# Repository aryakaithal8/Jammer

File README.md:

# Jammer

Jammer is my custom handheld electronics project, built around an **ESP32-S3-WROOM-1-N16** with a main board, a separate shield and a custom enclosure.

so basically i wanted to make a handheld device with its own screen, buttons, battery and a proper case, but i also wanted to go further than just connecting a bunch of ready-made modules together.. custom schematics, a stacked PCB design, touch display, storage, infrared, status feedback and the firmware side too. i designed the electronics in KiCad and worked on the enclosure in Fusion 360, which turned into a much bigger rabbit hole than expected lol

## why i made this

i wanted to build something where i could work on the whole thing from scratch instead of only doing one small part of it.. the circuit, board layout, case, controls and the parts list all had to fit together into one handheld project

main goals :

- make the schematic section by section in KiCad
- design a main board and a separate shield that fit together as a stack
- include a 2.8-inch SPI touch display and six front buttons
- include USB-C connections and a USB-to-UART interface for development
- add storage, infrared and visual feedback to the design
- plan the battery and power sections around a portable device
- work through PCB placement and routing instead of stopping at the schematic
- design a custom enclosure in Fusion 360
- keep the project files, production references, images and BOM together so the work is easier to understand and build on

the fun part is that everything affects everything else.. changing a connector position can affect the routing and the case opening, while changing the display arrangement can affect the buttons, internal space and cable clearance. thats the kind of detail that makes a handheld project way more involved than it looks from the outside

whats in this repo :

- `CAD/` — exported assembly models and printing files
- `BOM Images/` — supplier and component sourcing screenshots
- `Firmware/` — MicroPython application files and the bundled runtime image
- `FusionFiles/` — editable Fusion 360 design file
- `Images/` — PCB, schematic and enclosure screenshots
- `PCB/` — KiCad projects, libraries, audit material and the separate engineering revision
- `PDFs/` — exported schematic and layout PDFs
- `Production/` — Gerber archives, placement information, BOM and netlist exports
- `bom.csv` — sourcing list, supplier links and captured costs

## hardware summary

| | |
|---|---|
| Project | Jammer |
| Format | Custom handheld device with stacked main and shield boards |
| Controller listed in BOM | ESP32-S3-WROOM-1-N16 |
| Display | Robu 62026 2.8-inch SPI touch display |
| Front controls | Six buttons shown in the project design |
| USB | Two USB-C receptacles listed in the BOM |
| Development interface | CP2102N USB-to-UART section |
| Button interface in earlier design | PCF8574 I/O expander |
| Storage | SD card socket included in the design |
| Infrared | IR emitter and receiver parts included in the project |
| Feedback | Status LEDs, addressable RGB and a buzzer section |
| Radio parts in the supplied design material | nRF24L01-family and CC1101 parts with external connector provisions |
| Power | Battery, charging and supply sections with revision-specific parts |
| PCB | Main board and shield, with four-layer fabrication files in the revised engineering package |
| CAD | Fusion 360 and exported 3D files |
| Firmware | MicroPython source with hardware limitations documented in the files |

some of the interesting work is hidden inside the enclosure.. the boards need to fit together, the display needs its own space and support, and the controls and connectors need to line up with the outside of the case. the CAD and PCB images below show the project from a few different angles

## images

### main PCB

### PCB routing and board layers

### shield PCB

### schematic

i worked on the schematic in smaller sections first, then brought those sections together before moving into the PCB layout. the screenshots include the controller, power, connectors, display, controls and supporting circuits from the supplied design material

### CAD and case

these are design screenshots and renders, so they show the intended arrangement rather than a finished physical assembly. some schematic images also show earlier revisions and should be read alongside the current files

## repo file checklist

the main project folder names are:

- `PCB/` — KiCad design files and engineering references
- `CAD/` — assembly exports and printing files
- `FusionFiles/` — editable Fusion design
- `Firmware/` — MicroPython source and runtime files
- `Production/` — manufacturing outputs
- `PDFs/` — schematic and layout exports
- `Images/` — project screenshots used in this README
- `BOM Images/` — sourcing screenshots
- `bom.csv` — captured sourcing list

the exact filenames inside each folder may change as the project gets updated, so open the folders to find the relevant versions. check the revision before combining a schematic, board, firmware file or parts list from different places

## cad

the case was designed in Fusion 360. [`FusionFiles/Jammer V1.f3d`](FusionFiles/Jammer%20V1.f3d) is the editable design, while `CAD/` contains the exported assembly and printing material. check the available files and formats before preparing a print or manufacturing order

the case and PCB need to be checked together before fabrication: board mounting, screen support, connector access, button alignment and space for the battery and cables all matter. something looking clear in the outside render doesnt automatically mean the internal assembly fits properly

the internal CAD view is useful for seeing how the parts are intended to sit together, but the actual display module, connector tolerances and battery clearance still need a physical fit check

## firmware note

the project includes a `Firmware/` folder with MicroPython files for the application, hardware interfaces, display, storage, infrared and radio-related code. it also includes an ESP32-S3 MicroPython runtime image and its provenance information

the application source includes menu and device-status handling, touch calibration, storage/logging support and interface-related functions. these are source-level features and still need to be checked on the actual hardware

the top-level `hardware.py` explicitly sets `RADIOS_AVAILABLE = False`. it also holds some conflicting functions inactive instead of pretending they are usable, so the presence of a menu item or driver file isnt proof that the matching hardware feature is ready

firmware configuration and flashing details should be confirmed against the actual files and the matching schematic revision before building. i dont want to claim a particular image, pin assignment or feature is ready until it has been checked against the board it is meant to run on

## bom

the sourcing bill of materials is in [`bom.csv`](bom.csv). it includes the item name, quantity, supplier link, distributor and total line cost in US dollars.
**listed BOM total: $459.58 USD**

a few notable parts from the BOM:

| Part | Purpose |
|---|---|
| ESP32-S3-WROOM-1-N16 | Main controller |
| Robu 62026 touch display | Screen and touch interface |
| CP2102N-A02-GQFN28R | USB-to-UART interface |
| PCF8574T | I/O expansion in the earlier design |
| TE Connectivity 2041021-3 | SD card socket |
| GCT USB4105-GF-A | USB-C receptacles |
| WS2812B-2020-V6 | Addressable RGB indicators |
| CMT-7525-80-SMT-TR | Buzzer listed in the sourcing list |
| TSAL6200 and TSOP1738 | Infrared-related parts |
| nRF24L01 and CC1101 parts | Radio hardware represented in the supplied design material |
| Main and shield PCB fabrication | Separate board orders listed in the CSV |
| Printed enclosure and mounting hardware | Case and assembly parts |

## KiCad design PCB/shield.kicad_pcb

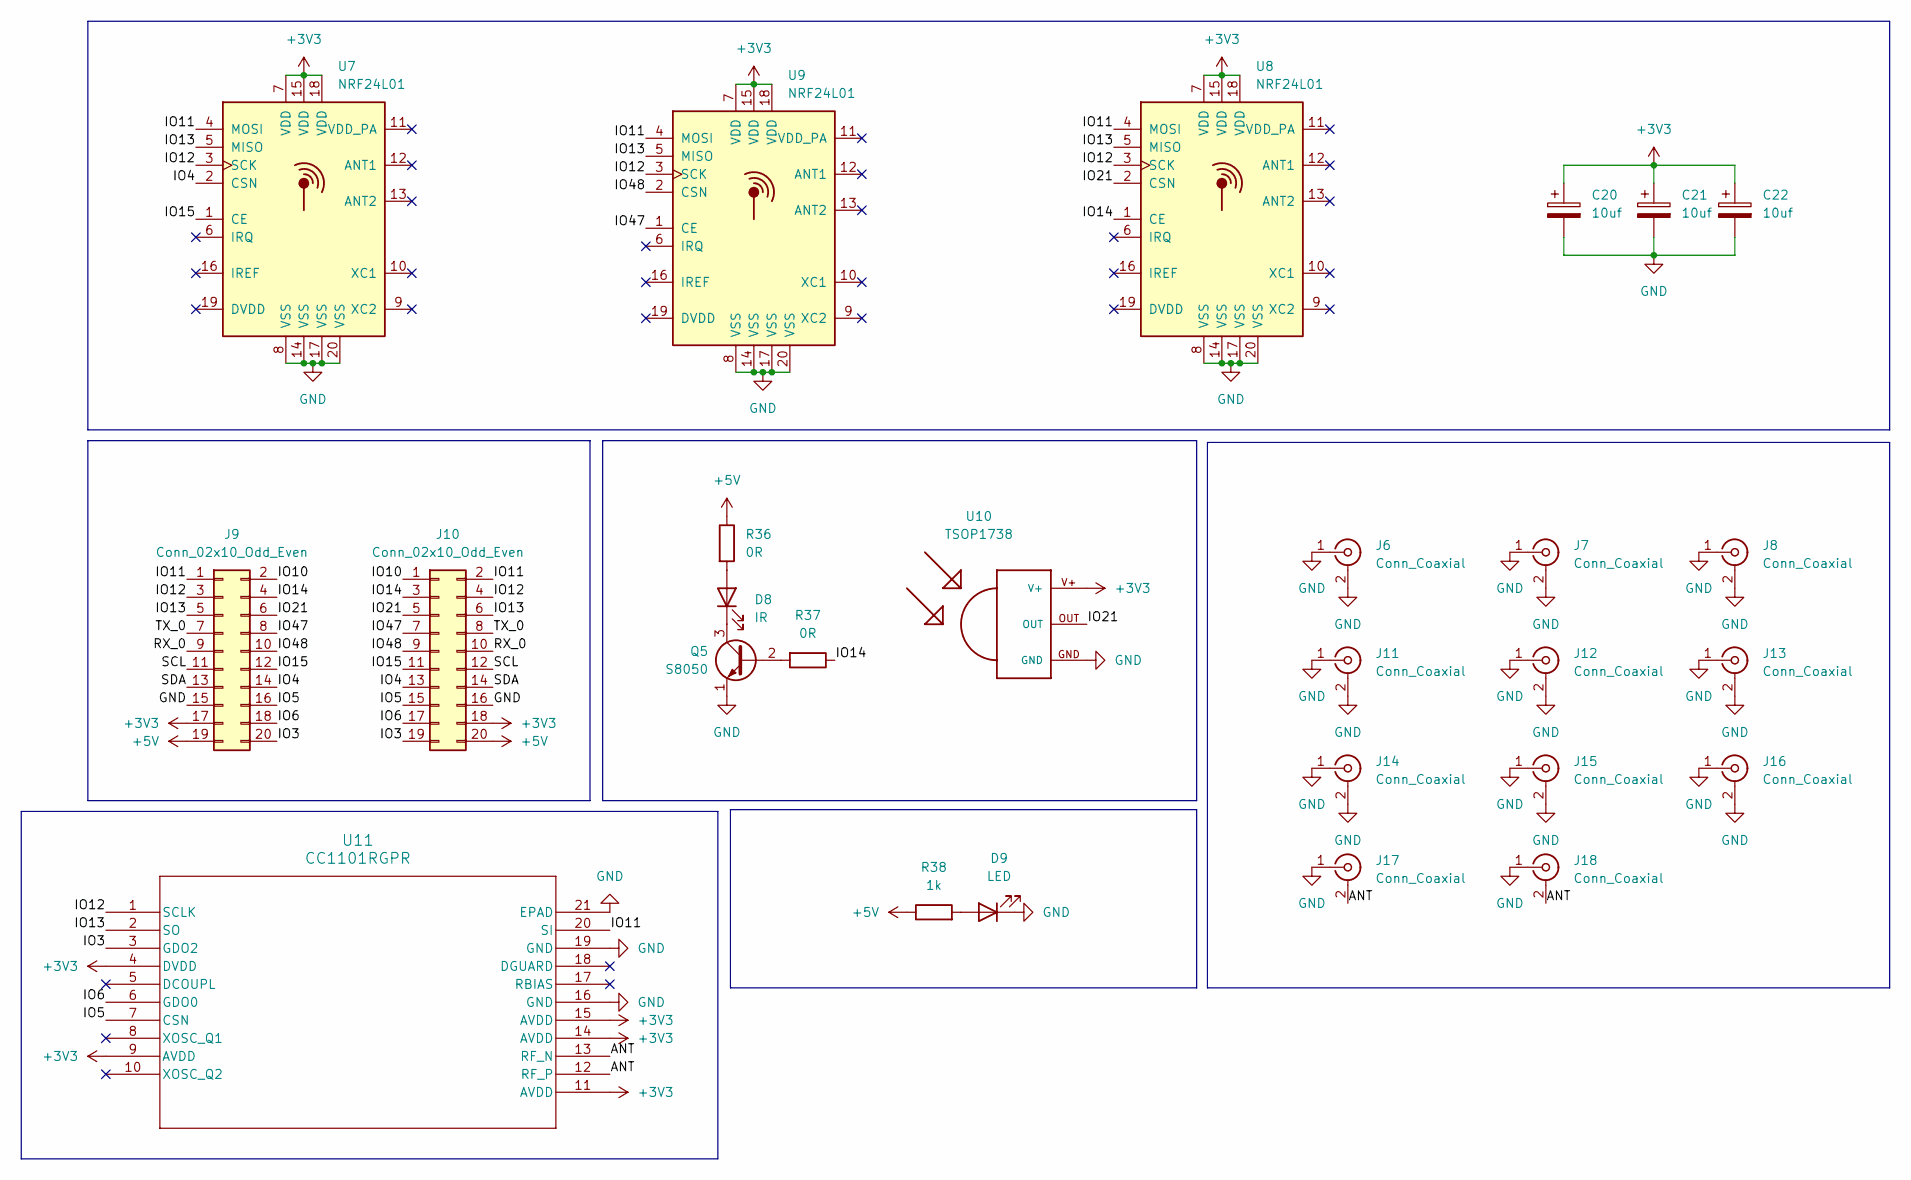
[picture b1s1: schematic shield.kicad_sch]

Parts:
C20, C21, C22: 10uf; C_0805_2012Metric
D8: IR; LED_D5.0mm
D9: LED; LED_0603_1608Metric
J6, J7, J8, J11, J12, J13, J14, J15, J16, J17, J18: Conn_Coaxial; SMA_Amphenol_132289_EdgeMount
J9, J10: Conn_02x10_Odd_Even; PinHeader_2x10_P2.54mm_Vertical
Q5: S8050; TO-92_Inline
R36, R37: 0R; R_0603_1608Metric
R38: 1k; R_0603_1608Metric
U7, U8, U9: NRF24L01; QFN-20-1EP_4x4mm_P0.5mm_EP2.5x2.5mm
U10: TSOP1738; TSOP17XX
U11: CC1101RGPR; RGP20_2P4X2P4

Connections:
+3V3: C20.1, C21.1, C22.1, J9.17, J10.18, U7.7 (VDD), U7.15 (VDD), U7.18 (VDD), U8.7 (VDD), U8.15 (VDD), U8.18 (VDD), U9.7 (VDD), U9.15 (VDD), U9.18 (VDD), U10.V+, U11.4 (DVDD), U11.9 (AVDD), U11.11 (AVDD), U11.14 (AVDD), U11.15 (AVDD)
+5V: J9.19, J10.20, R36.1, R38.1
/ANT: J17.2 (Ext), J18.2 (Ext), U11.12 (RF_P), U11.13 (RF_N)
/IO3: J9.20, J10.19, U11.3 (GDO2)
/IO4: J9.14, J10.13, U7.2 (CSN)
/IO5: J9.16, J10.15, U11.7 (CSN)
/IO6: J9.18, J10.17, U11.6 (GDO0)
/IO10: J9.2, J10.1
/IO11: J9.1, J10.2, U7.4 (MOSI), U8.4 (MOSI), U9.4 (MOSI), U11.20 (SI)
/IO12: J9.3, J10.4, U7.3 (SCK), U8.3 (SCK), U9.3 (SCK), U11.1 (SCLK)
/IO13: J9.5, J10.6, U7.5 (MISO), U8.5 (MISO), U9.5 (MISO), U11.2 (SO)
/IO14: J9.4, J10.3, R37.1, U8.1 (CE)
/IO15: J9.12, J10.11, U7.1 (CE)
/IO21: J9.6, J10.5, U8.2 (CSN), U10.OUT
/IO47: J9.8, J10.7, U9.1 (CE)
/IO48: J9.10, J10.9, U9.2 (CSN)
/RX_0: J9.9, J10.10
/SCL: J9.11, J10.12
/SDA: J9.13, J10.14
/TX_0: J9.7, J10.8
GND: C20.2, C21.2, C22.2, D9.1 (K), J6.1 (In), J6.2 (Ext), J7.1 (In), J7.2 (Ext), J8.1 (In), J8.2 (Ext), J9.15, J10.16, J11.1 (In), J11.2 (Ext), J12.1 (In), J12.2 (Ext), J13.1 (In), J13.2 (Ext), J14.1 (In), J14.2 (Ext), J15.1 (In), J15.2 (Ext), J16.1 (In), J16.2 (Ext), J17.1 (In), J18.1 (In), Q5.1 (E), U7.8 (VSS), U7.14 (VSS), U7.17 (VSS), U7.20 (VSS), U8.8 (VSS), U8.14 (VSS), U8.17 (VSS), U8.20 (VSS), U9.8 (VSS), U9.14 (VSS), U9.17 (VSS), U9.20 (VSS), U10.GND, U11.16 (GND), U11.19 (GND), U11.21 (EPAD)
unnamed: D8.2 (A), R36.2
unnamed: D8.1 (K), Q5.3 (C)
unnamed: D9.2 (A), R38.2
unnamed: Q5.2 (B), R37.2

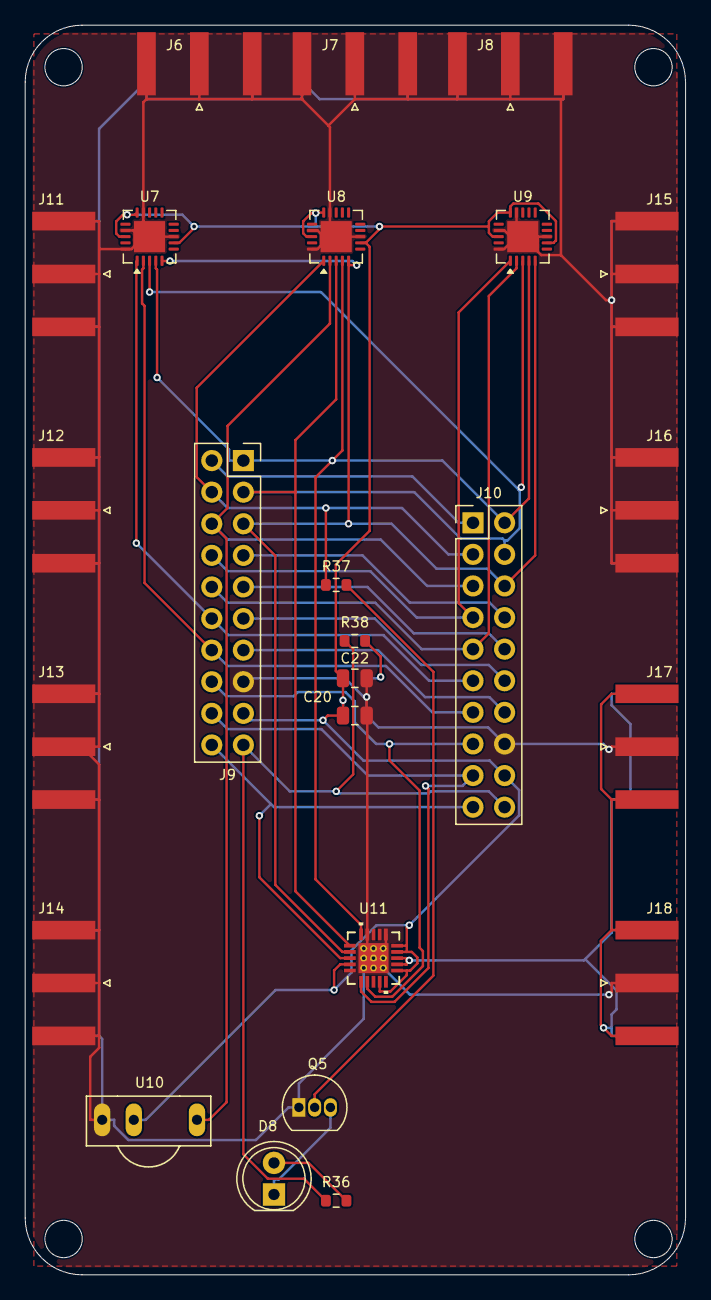
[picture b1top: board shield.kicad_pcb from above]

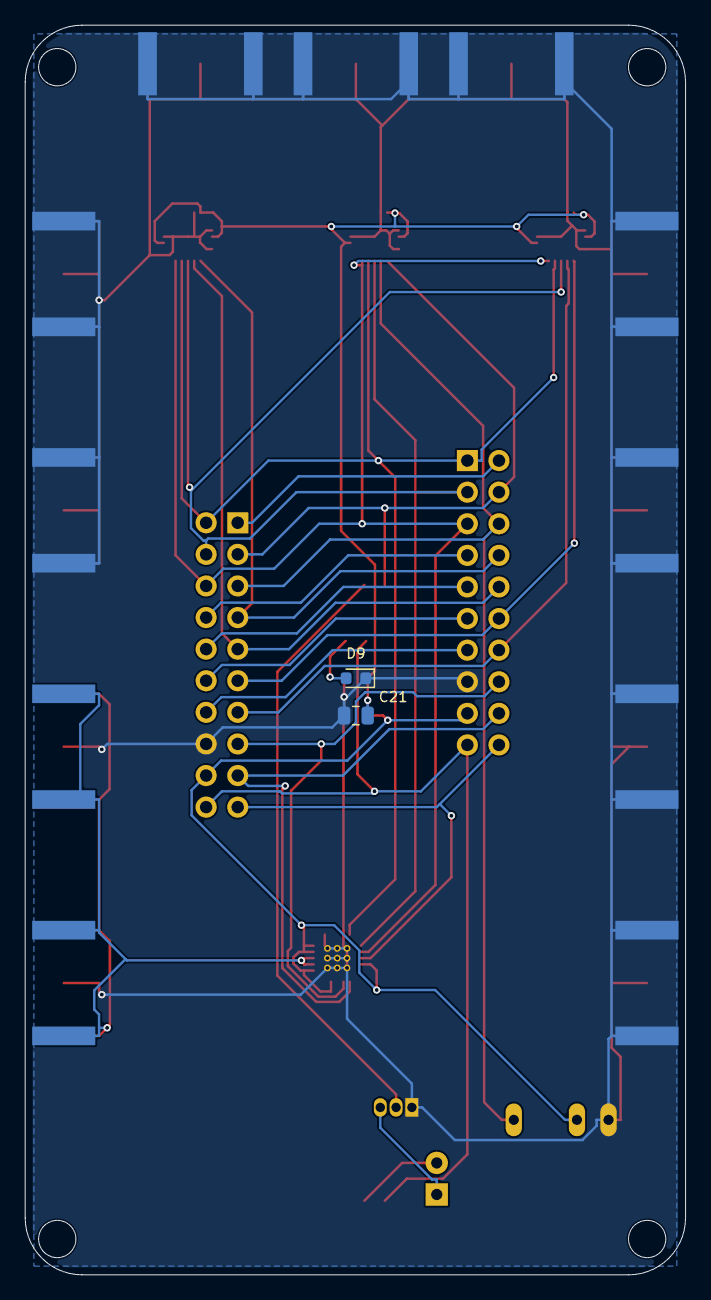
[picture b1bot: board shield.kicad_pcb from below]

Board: 2 copper layers, 53.1 x 100.5 mm, 31 parts (2 on the bottom side), 25 nets.

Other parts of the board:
H1, H2, H3, H4: M2.5 / 3 mm NPTH; MountingHole_3mm_M2p5

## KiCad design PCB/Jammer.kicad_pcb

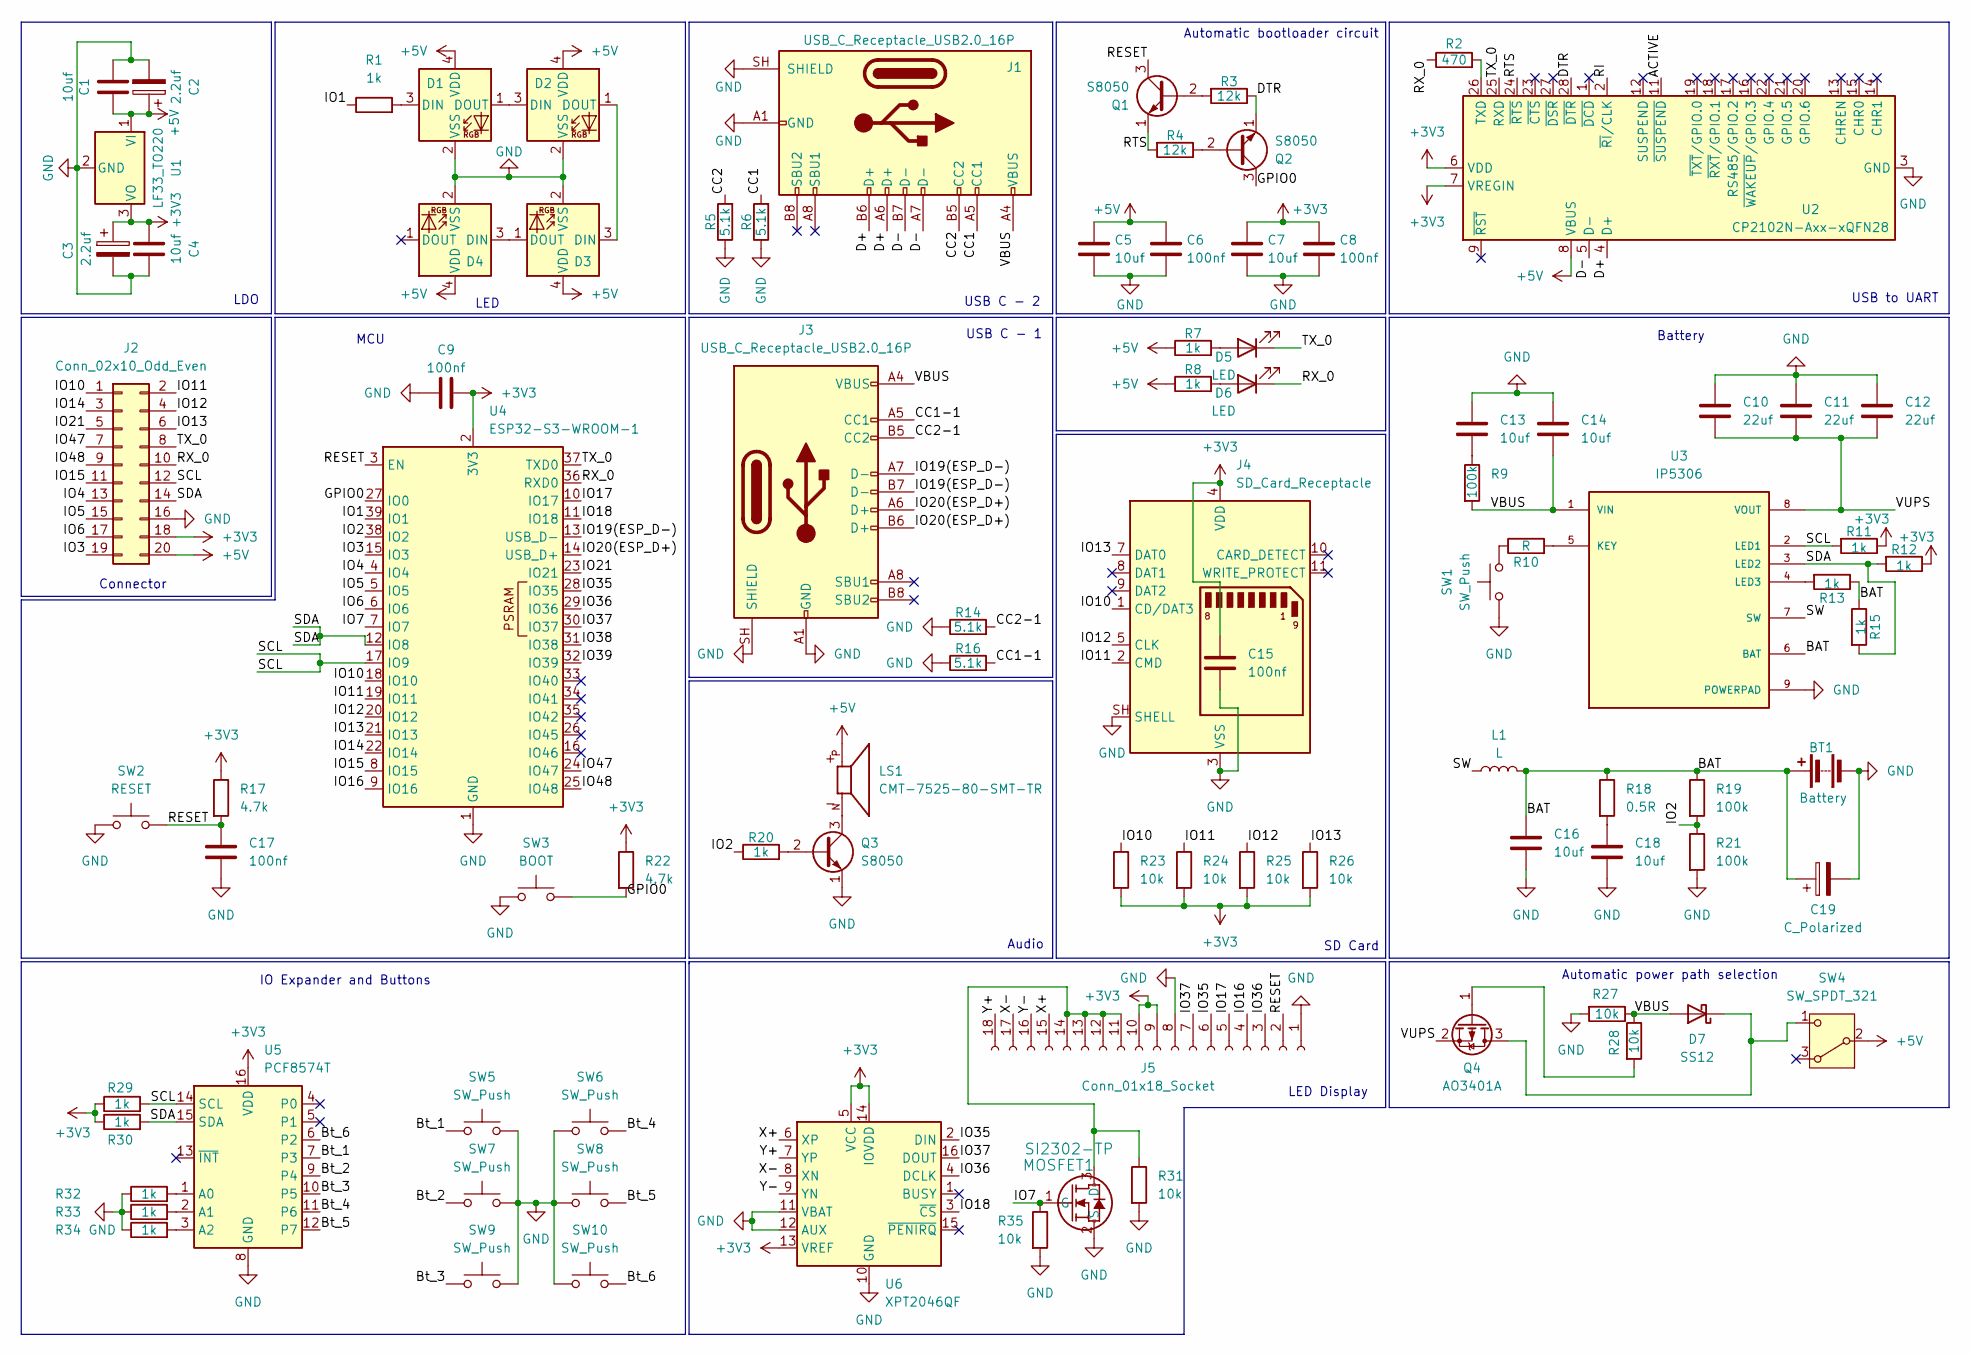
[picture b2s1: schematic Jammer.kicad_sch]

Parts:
BT1: Battery; PinHeader_1x02_P2.54mm_Vertical
C1, C4, C5, C7, C13, C14, C16, C18: 10uf; C_0603_1608Metric
C2, C3: 2.2uf; C_0805_2012Metric
C6, C8, C9, C15, C17: 100nf; C_0603_1608Metric
C10, C11, C12: 22uf; C_0603_1608Metric
C19: C_Polarized; C_0805_2012Metric
D1, D2, D3, D4: WS2812B-2020; LED_WS2812B-2020_PLCC4_2.0x2.0mm
D5, D6: LED; LED_0603_1608Metric
D7: SS12; D_SMA
J1, J3: USB_C_Receptacle_USB2.0_16P; USB_C_Receptacle_GCT_USB4105-xx-A_16P_TopMnt_Horizontal
J2: Conn_02x10_Odd_Even; PinHeader_2x10_P2.54mm_Vertical
J4: SD_Card_Receptacle; SD_TE_2041021
J5: Conn_01x18_Socket; PinHeader_1x18_P2.54mm_Vertical
L1: L; L_0603_1608Metric
LS1: CMT-7525-80-SMT-TR; XDCR_CMT-7525-80-SMT-TR; PARTREV N/A
MOSFET1: SI2302-TP; SOT-23
Q1, Q2, Q3: S8050; TO-92_Inline
Q4: AO3401A; SOT-23
R1: 1k
R2: 470; R_0603_1608Metric
R3, R4: 12k; R_0603_1608Metric
R5, R6, R14, R16: 5.1k; R_0603_1608Metric
R7, R8, R11, R12, R13, R15, R20, R29, R30, R32, R33, R34: 1k; R_0603_1608Metric
R9, R19, R21: 100k; R_0603_1608Metric
R10: R; R_0603_1608Metric
R17, R22: 4.7k; R_0603_1608Metric
R18: 0.5R; R_0603_1608Metric
R23, R24, R25, R26, R27, R28, R31, R35: 10k; R_0603_1608Metric
SW1, SW5, SW6, SW7, SW8, SW9, SW10: SW_Push; Panasonic_EVQPUJ_EVQPUA
SW2: RESET; Panasonic_EVQPUJ_EVQPUA
SW3: BOOT; Panasonic_EVQPUJ_EVQPUA
SW4: SW_SPDT_321; Panasonic_EVQPUJ_EVQPUA
U1: LF33_TO220; TO-220-3_Vertical
U2: CP2102N-Axx-xQFN28; QFN-28-1EP_5x5mm_P0.5mm_EP3.35x3.35mm
U3: IP5306; SOP127P600X165-9N; PARTREV 1.31
U4: ESP32-S3-WROOM-1
U5: PCF8574T; SOIC-16W_7.5x10.3mm_P1.27mm
U6: XPT2046QF; QFN-16-1EP_4x4mm_P0.65mm_EP2.1x2.1mm

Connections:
+3V3: C3.1, C4.1, C7.1, C8.1, C9.1, C15.1, J2.18, J4.4 (VDD), J5.9, J5.10, R11.1, R12.1, R17.1, R22.1, R23.2, R24.2, R25.2, R26.2, R29.1, R30.1, U1.3 (VO), U2.6 (VDD), U2.7 (VREGIN), U4.2 (3V3), U5.16 (VDD), U6.5 (VCC), U6.13 (VREF), U6.14 (IOVDD)
+5V: C1.1, C2.1, C5.1, C6.1, D1.4 (VDD), D2.4 (VDD), D3.4 (VDD), D4.4 (VDD), J2.20, LS1.P, R7.1, R8.1, SW4.2 (B), U1.1 (VI), U2.8 (VBUS)
/ACTIVE: U2.11 (~SUSPEND)
/BAT: BT1.1 (+), C16.1, C19.1, L1.2, R13.1, R15.1, R18.1, R19.1, U3.6 (BAT)
/Bt_1: SW5.1, U5.7 (P3)
/Bt_2: SW7.1, U5.9 (P4)
/Bt_3: SW9.1, U5.10 (P5)
/Bt_4: SW6.2, U5.11 (P6)
/Bt_5: SW8.2, U5.12 (P7)
/Bt_6: SW10.2, U5.6 (P2)
/CC1: J1.A5 (CC1), R6.2
/CC1-1: J3.A5 (CC1), R16.2
/CC2: J1.B5 (CC2), R5.2
/CC2-1: J3.B5 (CC2), R14.2
/D+: J1.A6 (D+), J1.B6 (D+), U2.4 (D+)
/D-: J1.A7 (D-), J1.B7 (D-), U2.5 (D-)
/DTR: Q2.1 (E), R3.1, U2.28 (~DTR)
/GPIO0: Q2.3 (C), R22.2, SW3.2, U4.27 (IO0)
/IO1: R1.1, U4.39 (IO1)
/IO2: R19.2, R20.1, R21.1, U4.38 (IO2)
/IO3: J2.19, U4.15 (IO3)
/IO4: J2.13, U4.4 (IO4)
/IO5: J2.15, U4.5 (IO5)
/IO6: J2.17, U4.6 (IO6)
/IO7: MOSFET1.1 (G), R35.1, U4.7 (IO7)
/IO10: J2.1, J4.1 (CD/DAT3), R23.1, U4.18 (IO10)
/IO11: J2.2, J4.2 (CMD), R24.1, U4.19 (IO11)
/IO12: J2.4, J4.5 (CLK), R25.1, U4.20 (IO12)
/IO13: J2.6, J4.7 (DAT0), R26.1, U4.21 (IO13)
/IO14: J2.3, U4.22 (IO14)
/IO15: J2.11, U4.8 (IO15)
/IO16: J5.4, U4.9 (IO16)
/IO17: J5.5, U4.10 (IO17)
/IO18: U4.11 (IO18), U6.3 (~CS)
/IO19(ESP_D-): J3.A7 (D-), J3.B7 (D-), U4.13 (USB_D-)
/IO20(ESP_D+): J3.A6 (D+), J3.B6 (D+), U4.14 (USB_D+)
/IO21: J2.5, U4.23 (IO21)
/IO35: J5.6, U4.28 (IO35), U6.2 (DIN)
/IO36: J5.3, U4.29 (IO36), U6.4 (DCLK)
/IO37: J5.7, U4.30 (IO37), U6.16 (DOUT)
/IO38: U4.31 (IO38)
/IO39: U4.32 (IO39)
/IO47: J2.7, U4.24 (IO47)
/IO48: J2.9, U4.25 (IO48)
/RESET: C17.1, J5.2, Q1.3 (C), R17.2, SW2.2, U4.3 (EN)
/RI: U2.2 (~RI/CLK)
/RTS: Q1.1 (E), R4.2, U2.24 (~RTS)
/RX_0: D6.1 (K), J2.10, R2.1, U4.36 (RXD0)
/SCL: J2.12, R11.2, R29.2, U3.2 (LED1), U4.17 (IO9), U5.14 (SCL)
/SDA: J2.14, R12.2, R15.2, R30.2, U3.3 (LED2), U4.12 (IO8), U5.15 (SDA)
/SW: L1.1, U3.7 (SW)
/TX_0: D5.1 (K), J2.8, U2.25 (RXD), U4.37 (TXD0)
/VBUS: C14.2, D7.2 (A), J1.A4 (VBUS), J1.A9 (VBUS), J1.B4 (VBUS), J1.B9 (VBUS), J3.A4 (VBUS), J3.A9 (VBUS), J3.B4 (VBUS), J3.B9 (VBUS), R9.2, R27.1, R28.1, U3.1 (VIN)
/VUPS: C10.2, C11.2, C12.2, Q4.2 (S), U3.8 (VOUT)
/X+: J5.15, U6.6 (XP)
/X-: J5.17, U6.8 (XN)
/Y+: J5.18, U6.7 (YP)
/Y-: J5.16, U6.9 (YN)
GND: BT1.2 (-), C1.2, C2.2, C3.2, C4.2, C5.2, C6.2, C7.2, C8.2, C9.2, C10.1, C11.1, C12.1, C13.1, C14.1, C15.2, C16.2, C17.2, C18.2, C19.2, D1.2 (VSS), D2.2 (VSS), D3.2 (VSS), D4.2 (VSS), J1.A1 (GND), J1.A12 (GND), J1.B1 (GND), J1.B12 (GND), J1.SH (SHIELD), J2.16, J3.A1 (GND), J3.A12 (GND), J3.B1 (GND), J3.B12 (GND), J3.SH (SHIELD), J4.3 (VSS), J4.6 (VSS), J4.SH (SHELL), J5.1, J5.8, MOSFET1.2 (S), Q3.1 (E), R5.1, R6.1, R14.1, R16.1, R21.2, R27.2, R31.2, R32.1, R33.1, R34.1, R35.2, SW1.1, SW2.1, SW3.1, SW5.2, SW6.1, SW7.2, SW8.1, SW9.2, SW10.1, U1.2 (GND), U2.3 (GND), U2.29 (GND), U3.9 (POWERPAD), U4.1 (GND), U4.40 (GND), U4.41 (GND), U5.8 (GND), U6.10 (GND), U6.11 (VBAT), U6.12 (AUX)
unnamed: C13.2, R9.1
unnamed: C18.1, R18.2
unnamed: D1.3 (DIN), R1.2
unnamed: D1.1 (DOUT), D2.3 (DIN)
unnamed: D2.1 (DOUT), D3.3 (DIN)
unnamed: D3.1 (DOUT), D4.3 (DIN)
unnamed: D5.2 (A), R7.2
unnamed: D6.2 (A), R8.2
unnamed: D7.1 (K), Q4.3 (D), SW4.1 (C)
unnamed: J5.11, J5.12, J5.13, J5.14, MOSFET1.3 (D), R31.1
unnamed: Q1.2 (B), R3.2
unnamed: Q2.2 (B), R4.1
unnamed: Q3.2 (B), R20.2
unnamed: LS1.N, Q3.3 (C)
unnamed: Q4.1 (G), R28.2
unnamed: R10.1, SW1.2
unnamed: R2.2, U2.26 (TXD)
unnamed: R10.2, U3.5 (KEY)
unnamed: R13.2, U3.4 (LED3)
unnamed: R32.2, U5.1 (A0)
unnamed: R33.2, U5.2 (A1)
unnamed: R34.2, U5.3 (A2)

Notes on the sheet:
SD Card
LED
USB C - 1
Battery
Automatic power path selection
IO Expander and Buttons
Connector
MCU
USB to UART
Automatic bootloader circuit
LDO
USB C - 2
LED Display
Audio

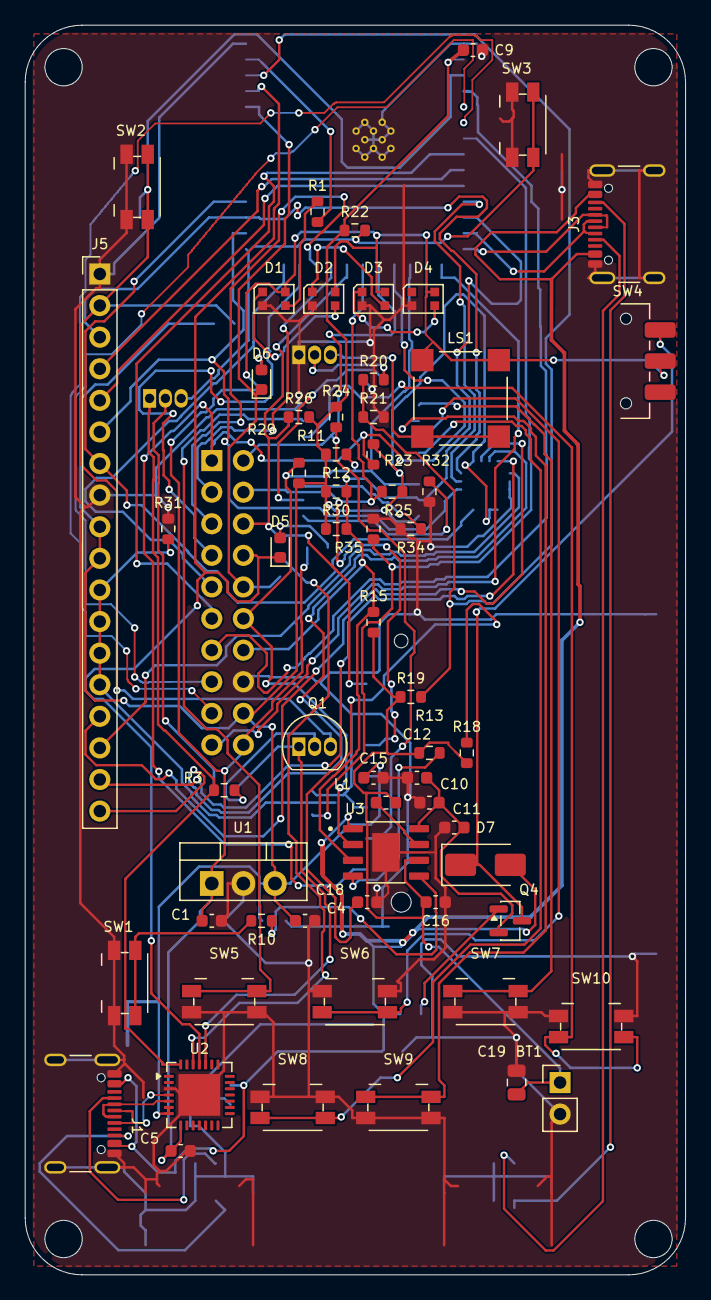
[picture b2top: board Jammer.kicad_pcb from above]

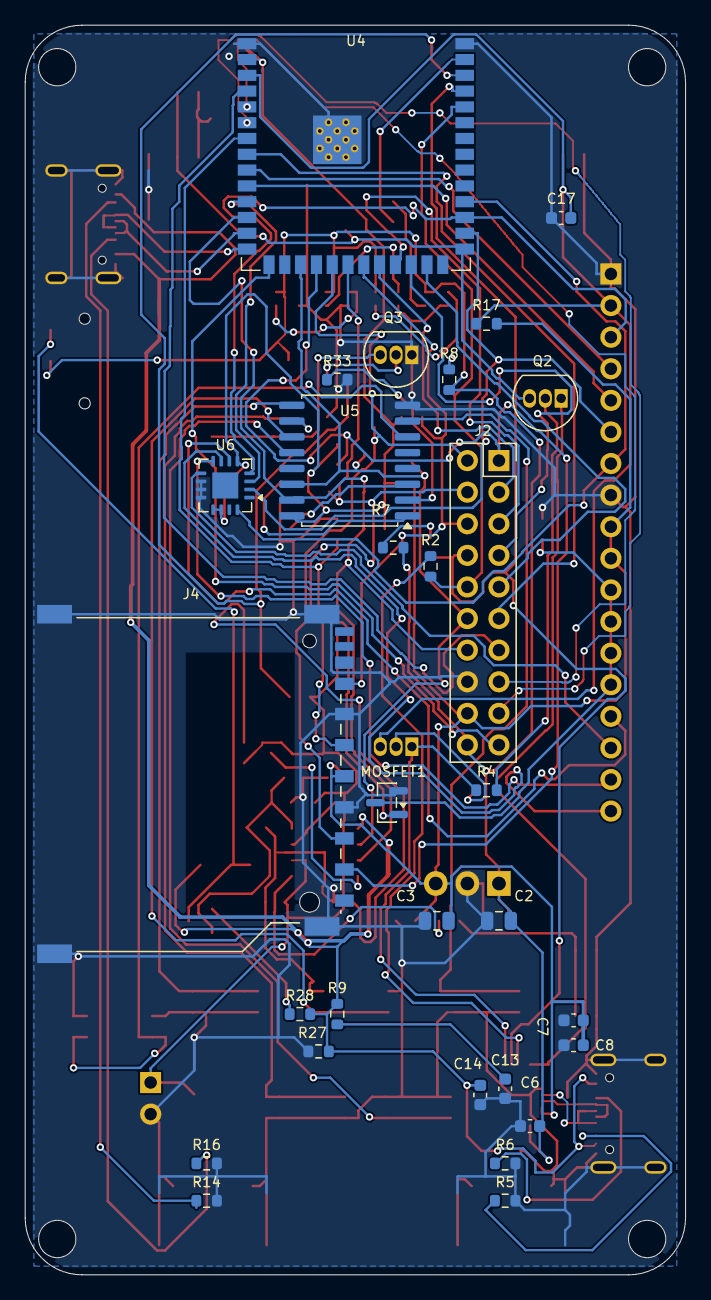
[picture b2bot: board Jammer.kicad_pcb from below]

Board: 2 copper layers, 53.1 x 100.5 mm, 94 parts (29 on the bottom side), 77 nets.

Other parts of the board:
H1, H2, H3, H4: M2.5 / 3 mm NPTH; MountingHole_3mm_M2p5
